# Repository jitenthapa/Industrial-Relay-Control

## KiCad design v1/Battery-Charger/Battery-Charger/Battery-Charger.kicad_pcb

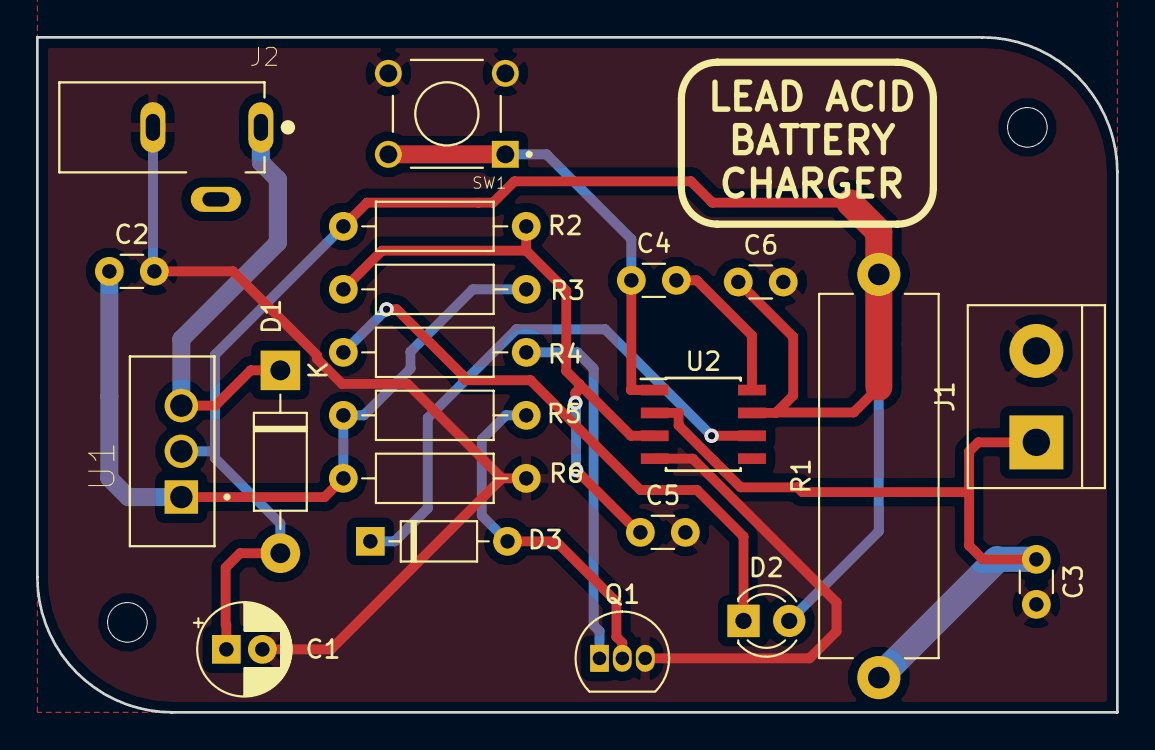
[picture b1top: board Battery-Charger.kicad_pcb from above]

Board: 2 copper layers, 60.0 x 37.5 mm, 23 parts (0 on the bottom side), 12 nets.

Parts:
C1: CP; CP_Radial_D5.0mm_P2.00mm
C2, C3, C4: C_Small; C_Disc_D3.0mm_W1.6mm_P2.50mm
C5: 10pf; C_Disc_D3.0mm_W1.6mm_P2.50mm
C6: 100nf; C_Disc_D3.0mm_W1.6mm_P2.50mm
D1: 1N4007; D_DO-41_SOD81_P10.16mm_Horizontal
D2: LED; LED_D3.0mm
D3: 1N4148; D_DO-35_SOD27_P7.62mm_Horizontal
J1: BATTERY; TerminalBlock_bornier-2_P5.08mm
J2: Jack-DC; DC-JACK
MOUNT1, MOUNT2: MountingHole_2.2mm_M2
Q1: 2N3906; TO-92_Inline
R1: R_Small; R_Axial_Power_L20.0mm_W6.4mm_P22.40mm
R2, R3: R_Small; R_Axial_DIN0207_L6.3mm_D2.5mm_P10.16mm_Horizontal
R4, R5, R6: R; R_Axial_DIN0207_L6.3mm_D2.5mm_P10.16mm_Horizontal
SW1: 1825910-2; TE_1825910-2
U1: LM338T; TO254P1054X470X1955-3
U2: LM301; SOIC-8_3.9x4.9mm_P1.27mm

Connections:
GND: C1.2, C2.2, C3.2, C5.2, C6.2, J1.2, J2.2, Q1.3, R6.2, SW1.3, SW1.4, U2.4
unnamed: C1.1, C6.1, D1.2, D2.2, R1.2, R2.1, U1.2, U2.7
unnamed: C2.1, R3.2, R5.1, R6.1, U1.1
unnamed: C3.1, J1.1, R1.1, U2.2
unnamed: C4.1, SW1.1, SW1.2, U2.1
unnamed: C4.2, U2.8
unnamed: C5.1, R2.2, R3.1, U2.3
unnamed: D1.1, J2.1, U1.3
unnamed: D2.1, R4.1
unnamed: D3.1, U2.6
unnamed: D3.2, Q1.2, R5.2
unnamed: Q1.1, R4.2

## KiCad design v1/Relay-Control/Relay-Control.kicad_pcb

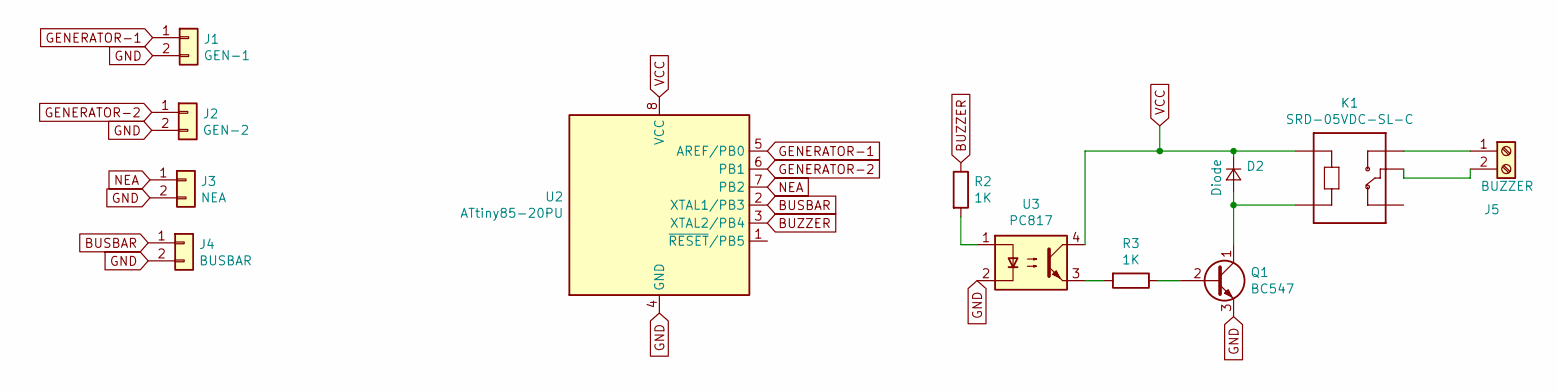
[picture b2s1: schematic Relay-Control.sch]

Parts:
D2: Diode; D_DO-27_P12.70mm_Horizontal
J1: GEN-1; Pin_Header_Straight_1x02_Pitch2.54mm
J2: GEN-2; Pin_Header_Straight_1x02_Pitch2.54mm
J3: NEA; Pin_Header_Straight_1x02_Pitch2.54mm
J4: BUSBAR; Pin_Header_Straight_1x02_Pitch2.54mm
J5: BUZZER; dual terminal-small-2
K1: SRD-05VDC-SL-C; RELAY_SRD-05VDC-SL-C
Q1: BC547; TO-92_Inline
R2, R3: 1K; R_0805_2012Metric
U2: ATtiny85-20PU; DIP-8_W7.62mm
U3: PC817; DIP-4_W7.62mm

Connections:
BUSBAR: J4.1, U2.2 (XTAL1/PB3)
BUZZER: R2.1, U2.3 (XTAL2/PB4)
GENERATOR-1: J1.1, U2.5 (AREF/PB0)
GENERATOR-2: J2.1, U2.6 (PB1)
GND: J1.2, J2.2, J3.2, J4.2, Q1.3 (E), U2.4 (GND), U3.2
NEA: J3.1, U2.7 (PB2)
unnamed: D2.2 (A), K1.A2, Q1.1 (C)
unnamed: J5.1, K1.NO
unnamed: J5.2, K1.COM
unnamed: Q1.2 (B), R3.1
unnamed: R2.2, U3.1
unnamed: R3.2, U3.3
VCC: D2.1 (K), K1.A1, U2.8 (VCC), U3.4

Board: 2 copper layers, 12 parts (0 on the bottom side), 13 nets, no tracks yet.

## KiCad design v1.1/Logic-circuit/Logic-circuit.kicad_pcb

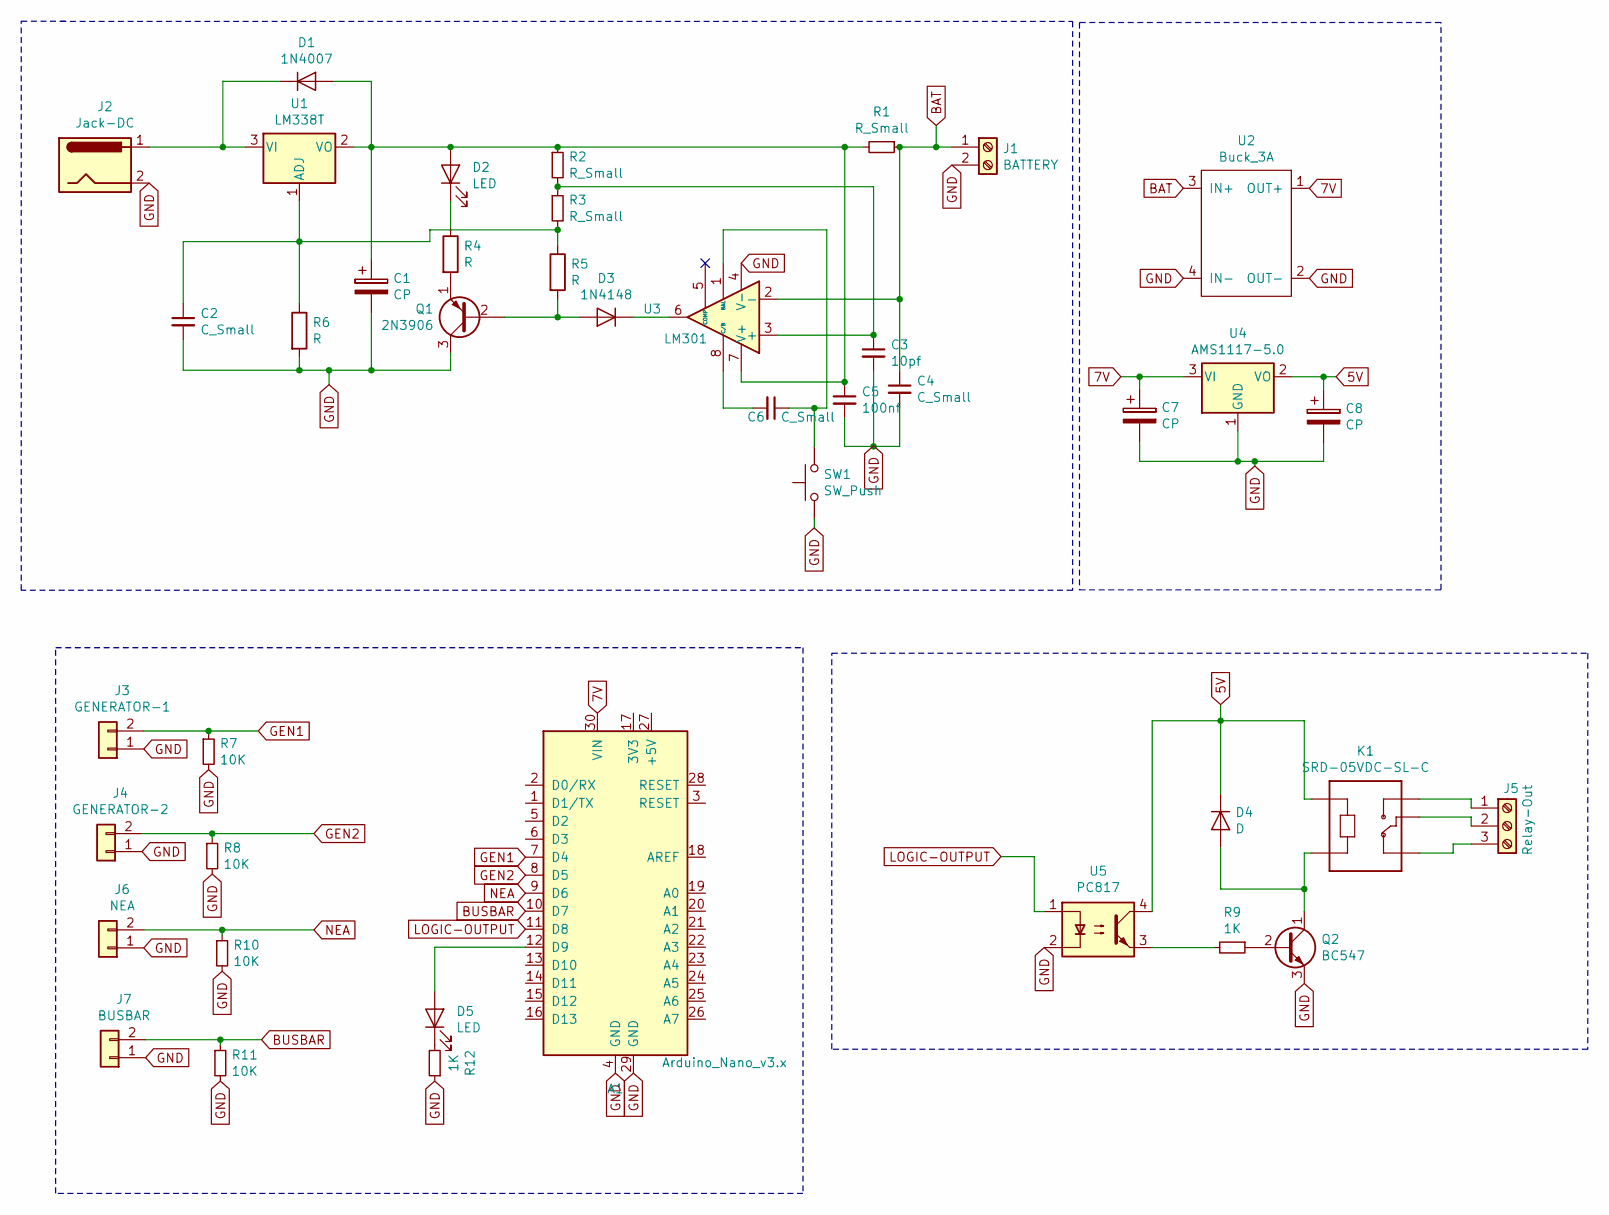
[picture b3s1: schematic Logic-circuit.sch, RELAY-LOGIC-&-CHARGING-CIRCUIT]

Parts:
A1: Arduino_Nano_v3.x; Arduino_Nano
C1, C7, C8: CP; CP_Radial_D5.0mm_P2.00mm
C2, C4, C6: C_Small; C_Disc_D3.0mm_W1.6mm_P2.50mm
C3: 10pf; C_Disc_D3.0mm_W1.6mm_P2.50mm
C5: 100nf; C_Disc_D3.0mm_W1.6mm_P2.50mm
D1: 1N4007; D_DO-41_SOD81_P10.16mm_Horizontal
D2, D5: LED; LED_D3.0mm
D3: 1N4148; D_DO-35_SOD27_P7.62mm_Horizontal
D4: D; D_SMA
J1: BATTERY; TerminalBlock_bornier-2_P5.08mm
J2: Jack-DC; DCJ200-10-A-XX-X_REVA
J3: GENERATOR-1; PinHeader_1x02_P2.54mm_Vertical
J4: GENERATOR-2; PinHeader_1x02_P2.54mm_Vertical
J5: Relay-Out; TerminalBlock_bornier-3_P5.08mm
J6: NEA; PinHeader_1x02_P2.54mm_Vertical
J7: BUSBAR; PinHeader_1x02_P2.54mm_Vertical
K1: SRD-05VDC-SL-C; RELAY_SRD-05VDC-SL-C-2
Q1: 2N3906; TO-92_Inline
Q2: BC547; TO-92_Inline
R1: R_Small; R_Axial_Power_L20.0mm_W6.4mm_P22.40mm
R2, R3: R_Small; R_Axial_DIN0207_L6.3mm_D2.5mm_P10.16mm_Horizontal
R4, R5, R6: R; R_Axial_DIN0207_L6.3mm_D2.5mm_P10.16mm_Horizontal
R7, R8, R10, R11: 10K; R_0805_2012Metric
R9, R12: 1K; R_0805_2012Metric
SW1: SW_Push; TE_1825910-2
U1: LM338T; TO-220-3_Vertical
U2: Buck_3A; Buck_3A-2
U3: LM301; SOIC-8_3.9x4.9mm_P1.27mm
U4: AMS1117-5.0; SOT-223-3_TabPin2
U5: PC817; DIP-4_W7.62mm

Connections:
5V: C8.1, D4.1 (K), K1.A1, U4.2 (VO), U5.4
7V: A1.30 (VIN), C7.1, U2.1 (OUT+), U4.3 (VI)
BAT: C4.1, J1.1, R1.1, U2.3 (IN+), U3.2 (-)
BUSBAR: A1.10 (D7), J7.2, R11.1
GEN1: A1.7 (D4), J3.2, R7.1
GEN2: A1.8 (D5), J4.2, R8.1
GND: A1.4 (GND), A1.29 (GND), C1.2, C2.2, C3.2, C4.2, C5.2, C7.2, C8.2, J1.2, J2.2, J3.1, J4.1, J6.1, J7.1, Q1.3 (C), Q2.3 (E), R6.2, R7.2, R8.2, R10.2, R11.2, R12.1, SW1.1, U2.2 (OUT-), U2.4 (IN-), U3.4 (V-), U4.1 (GND), U5.2
LOGIC-OUTPUT: A1.11 (D8), U5.1
NEA: A1.9 (D6), J6.2, R10.1
unnamed: A1.12 (D9), D5.2 (A)
unnamed: C1.1, C5.1, D1.2 (A), D2.2 (A), R1.2, R2.1, U1.2 (VO), U3.7 (V+)
unnamed: C2.1, R3.2, R5.1, R6.1, U1.1 (ADJ)
unnamed: C3.1, R2.2, R3.1, U3.3 (+)
unnamed: C6.1, SW1.2, U3.1 (BAL)
unnamed: C6.2, U3.8 (C/B)
unnamed: D1.1 (K), J2.1, U1.3 (VI)
unnamed: D2.1 (K), R4.1
unnamed: D3.1 (K), U3.6
unnamed: D3.2 (A), Q1.2 (B), R5.2
unnamed: D4.2 (A), K1.A2, Q2.1 (C)
unnamed: D5.1 (K), R12.2
unnamed: J5.1, K1.NO
unnamed: J5.2, K1.COM
unnamed: J5.3, K1.NC
unnamed: Q1.1 (E), R4.2
unnamed: Q2.2 (B), R9.1
unnamed: R9.2, U5.3

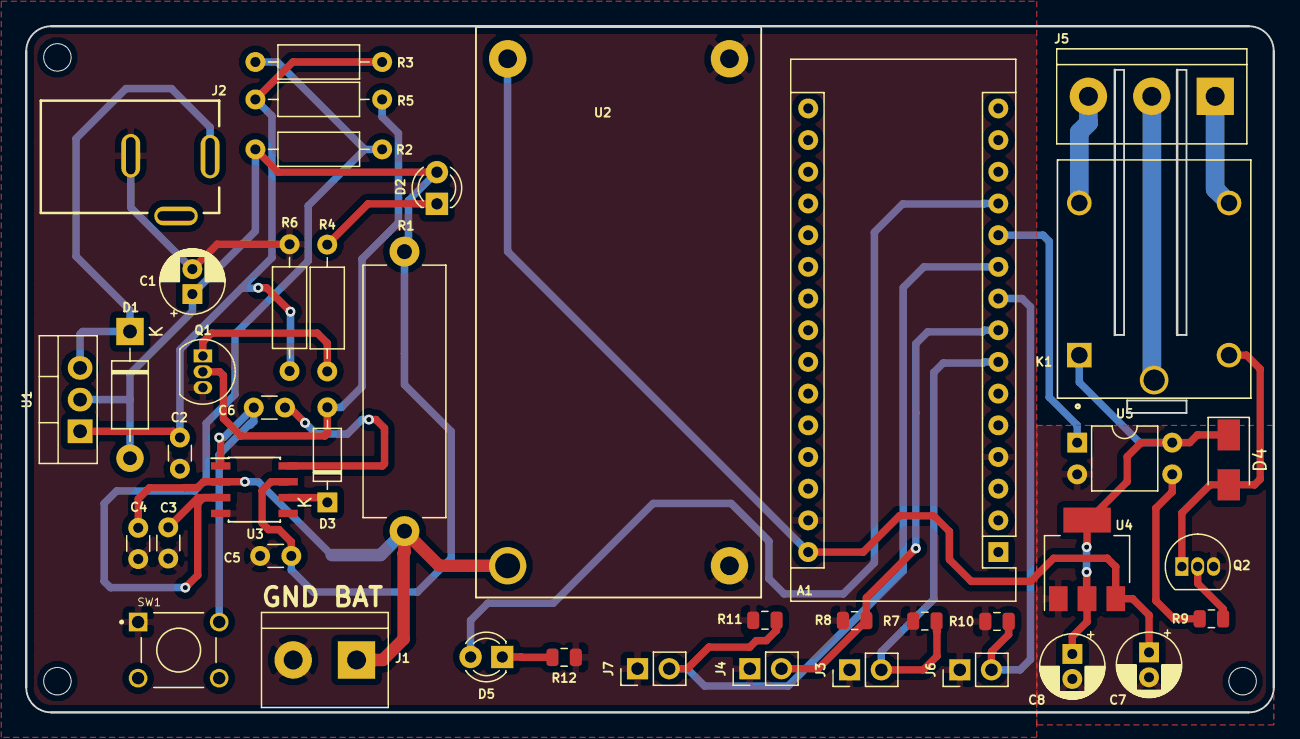
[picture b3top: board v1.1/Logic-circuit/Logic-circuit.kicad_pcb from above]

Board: 2 copper layers, 100.0 x 55.0 mm, 45 parts (0 on the bottom side), 27 nets.

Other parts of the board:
MH1, MH2, MH3: MountingHole_2.2mm_M2

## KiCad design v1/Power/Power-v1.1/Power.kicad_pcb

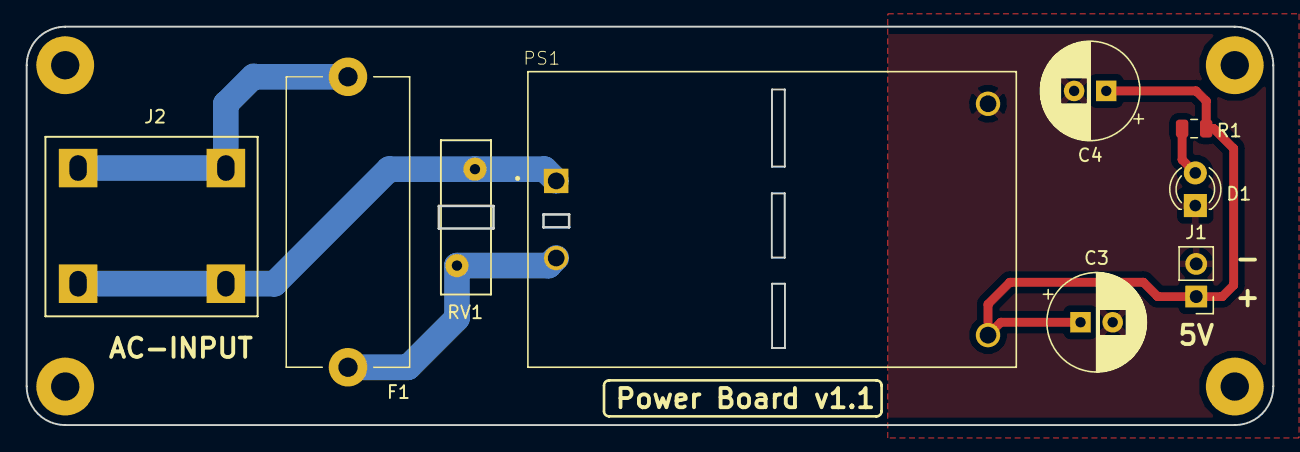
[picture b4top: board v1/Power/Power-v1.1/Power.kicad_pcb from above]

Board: 2 copper layers, 97.0 x 31.0 mm, 13 parts (0 on the bottom side), 6 nets.

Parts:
C3: 220uf; CP_Radial_D7.5mm_P2.50mm
C4: 1uf; CP_Radial_D7.5mm_P2.50mm
D1: LED; LED_D3.0mm
F1: Fuse; Fuseholder_Cylinder-5x20mm_Stelvio-Kontek_PTF78_Horizontal_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
J1: DC-POWER; Pin_Header_Straight_1x02_Pitch2.54mm
J2: AC; dual terminal-large
MH1, MH2, MH2#2, MH2#3: MountingHole_2.2mm_M2
PS1: POWER SUPPLY; CONV_HLK-5M05-Large-holes
R1: 220; R_0805_2012Metric
RV1: Varistor; RV_Disc_D12mm_W3.9mm_P7.5mm

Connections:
5V: C3.1, C4.1, J1.1, PS1.4, R1.2
GND: C3.2, C4.2, D1.1, J1.2, PS1.3
unnamed: D1.2, R1.1
unnamed: F1.1, PS1.2, RV1.1
unnamed: F1.2, J2.2
unnamed: J2.1, PS1.1, RV1.2

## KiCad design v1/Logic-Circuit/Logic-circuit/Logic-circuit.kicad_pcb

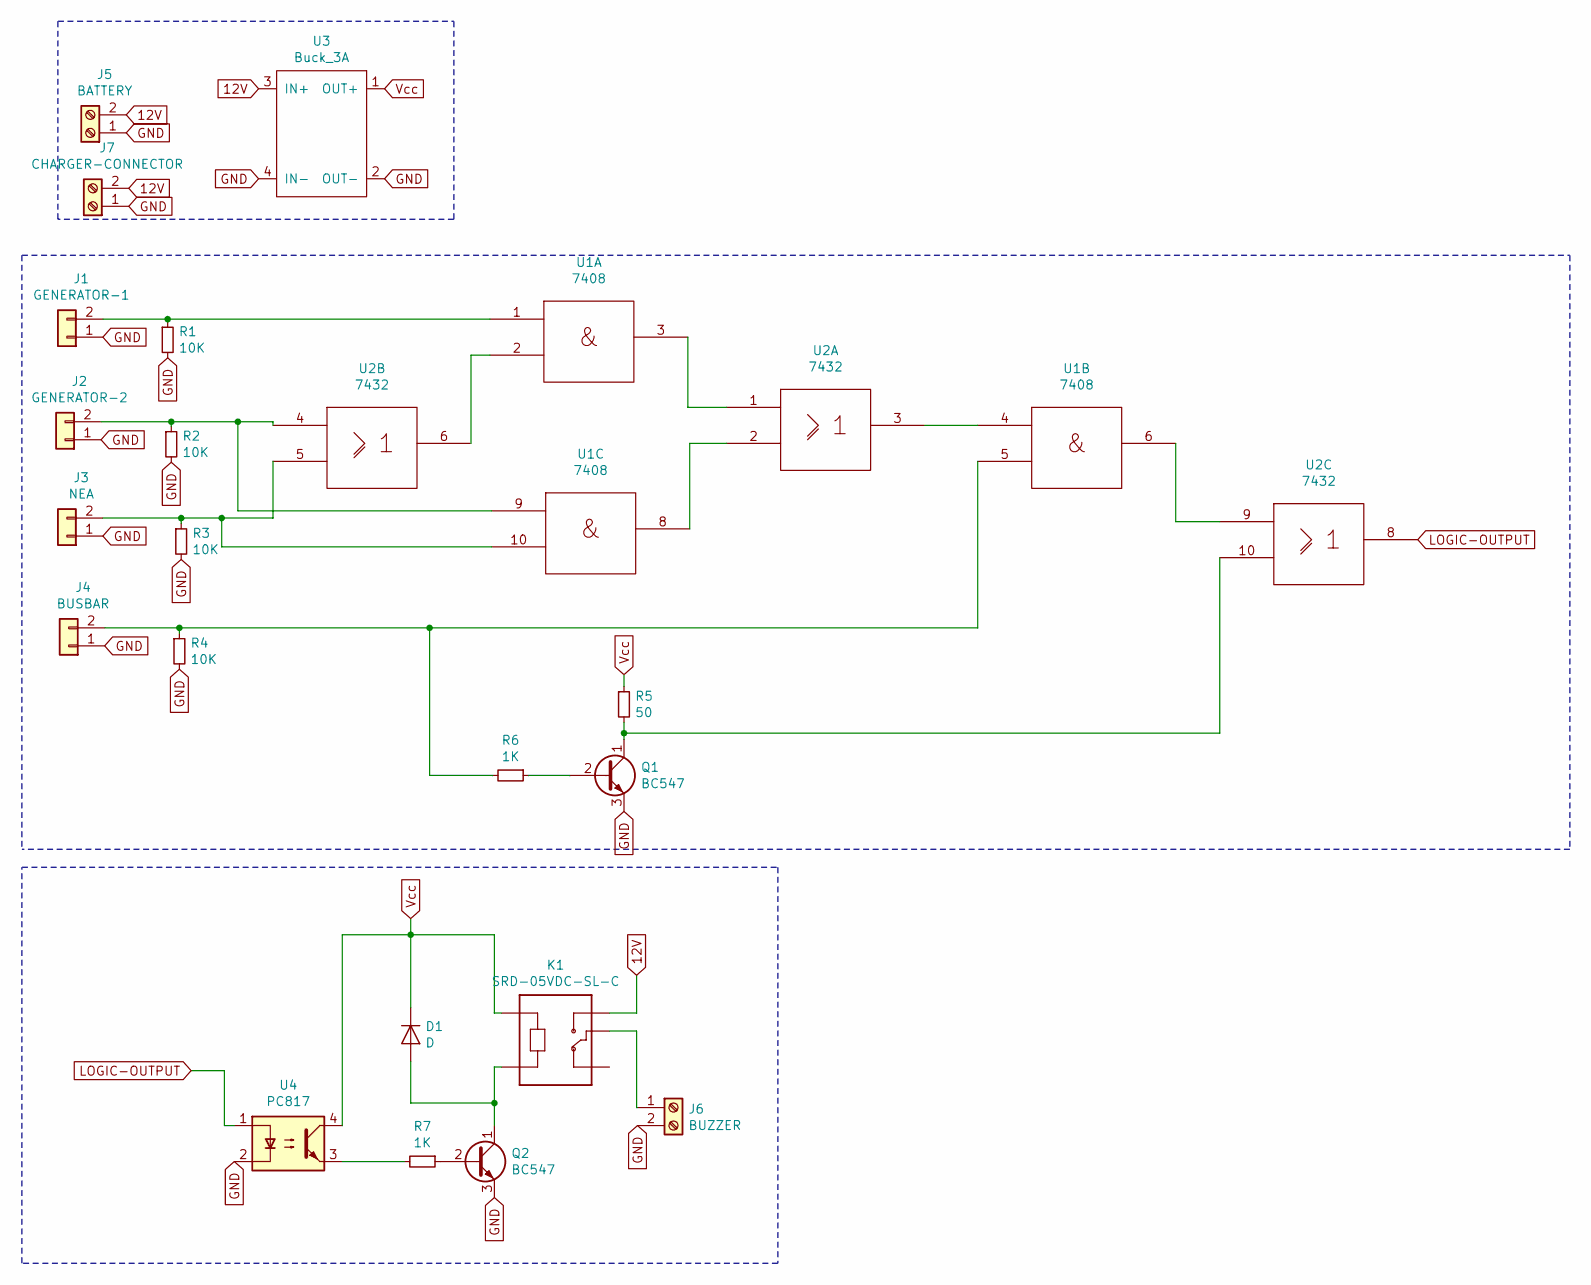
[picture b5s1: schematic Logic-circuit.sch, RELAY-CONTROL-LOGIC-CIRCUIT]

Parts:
D1: D; D_SOD-123
J1: GENERATOR-1; PinHeader_1x02_P2.54mm_Vertical
J2: GENERATOR-2; PinHeader_1x02_P2.54mm_Vertical
J3: NEA; PinHeader_1x02_P2.54mm_Vertical
J4: BUSBAR; PinHeader_1x02_P2.54mm_Vertical
J5: BATTERY; TerminalBlock_bornier-2_P5.08mm
J6: BUZZER; TerminalBlock_bornier-2_P5.08mm
J7: CHARGER-CONNECTOR; TerminalBlock_bornier-2_P5.08mm
K1: SRD-05VDC-SL-C; RELAY_SRD-05VDC-SL-C-2
Q1, Q2: BC547; TO-92_Inline
R1, R2, R3, R4: 10K; R_0805_2012Metric
R5: 50; R_0805_2012Metric
R6, R7: 1K; R_0805_2012Metric
U1: 7408; DIP-14_W7.62mm
U2: 7432; DIP-14_W7.62mm
U3: Buck_3A; Buck_3A-2
U4: PC817; DIP-4_W7.62mm

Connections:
12V: J5.2, J7.2, K1.NO, U3.3 (IN+)
GND: J1.1, J2.1, J3.1, J4.1, J5.1, J6.2, J7.1, Q1.3 (E), Q2.3 (E), R1.2, R2.2, R3.2, R4.2, U3.2 (OUT-), U3.4 (IN-), U4.2
Gnd: U1.7 (Gnd), U2.7 (Gnd)
LOGIC-OUTPUT: U2.8, U4.1
unnamed: D1.2 (A), K1.A2, Q2.1 (C)
unnamed: J1.2, R1.1, U1.1
unnamed: J2.2, R2.1, U1.9, U2.4
unnamed: J3.2, R3.1, U1.10, U2.5
unnamed: J4.2, R4.1, R6.2, U1.5
unnamed: J6.1, K1.COM
unnamed: Q1.1 (C), R5.2, U2.10
unnamed: Q1.2 (B), R6.1
unnamed: Q2.2 (B), R7.1
unnamed: R7.2, U4.3
unnamed: U1.2, U2.6
unnamed: U1.3, U2.1
unnamed: U1.4, U2.3
unnamed: U1.6, U2.9
unnamed: U1.8, U2.2
Vcc: D1.1 (K), K1.A1, R5.1, U1.14 (Vcc), U2.14 (Vcc), U3.1 (OUT+), U4.4

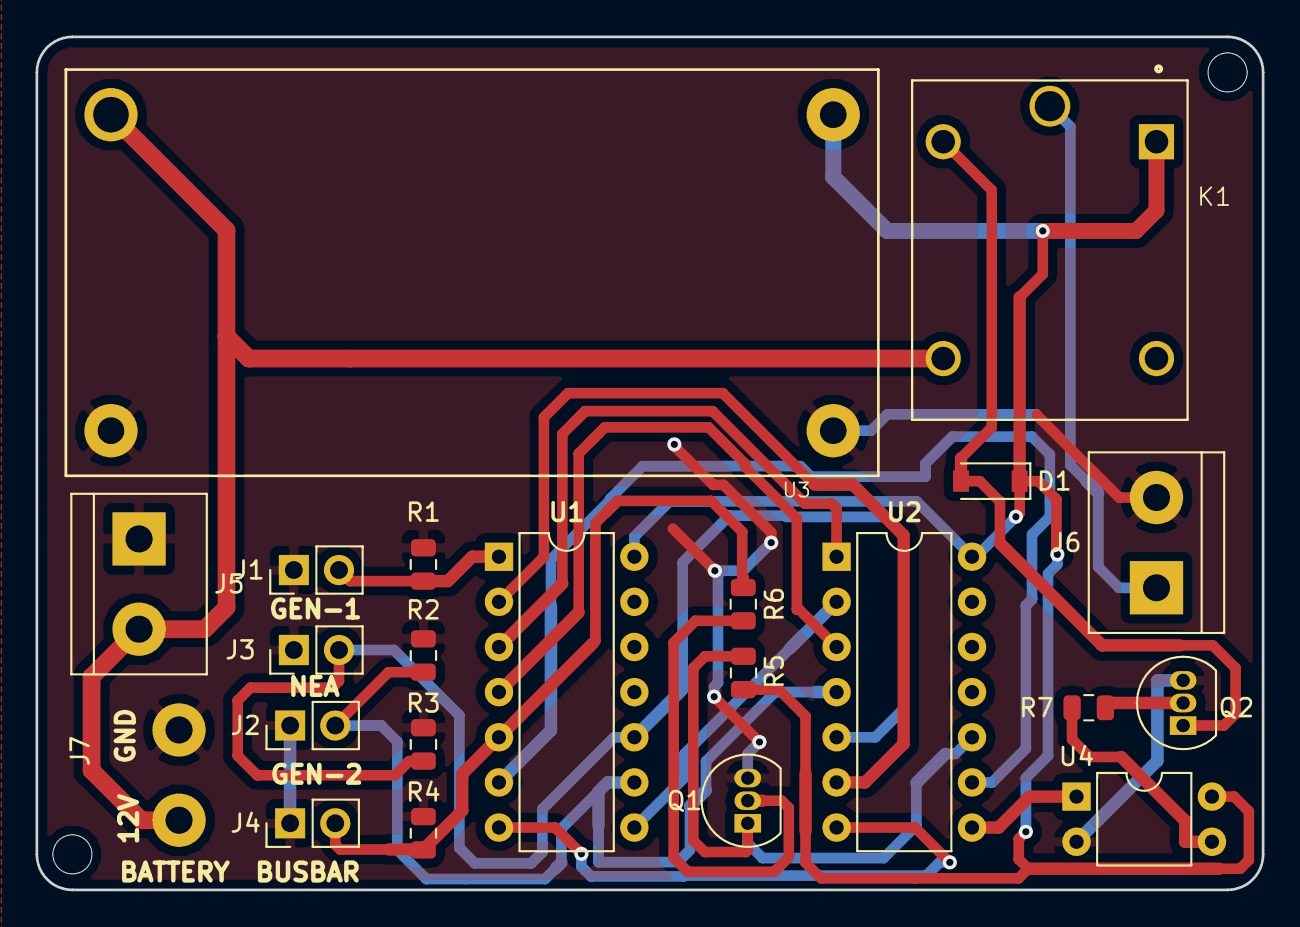
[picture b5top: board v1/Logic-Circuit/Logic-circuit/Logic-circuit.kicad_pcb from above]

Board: 2 copper layers, 69.0 x 48.0 mm, 24 parts (0 on the bottom side), 20 nets.

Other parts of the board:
MH1, MH2: MountingHole_2.2mm_M2

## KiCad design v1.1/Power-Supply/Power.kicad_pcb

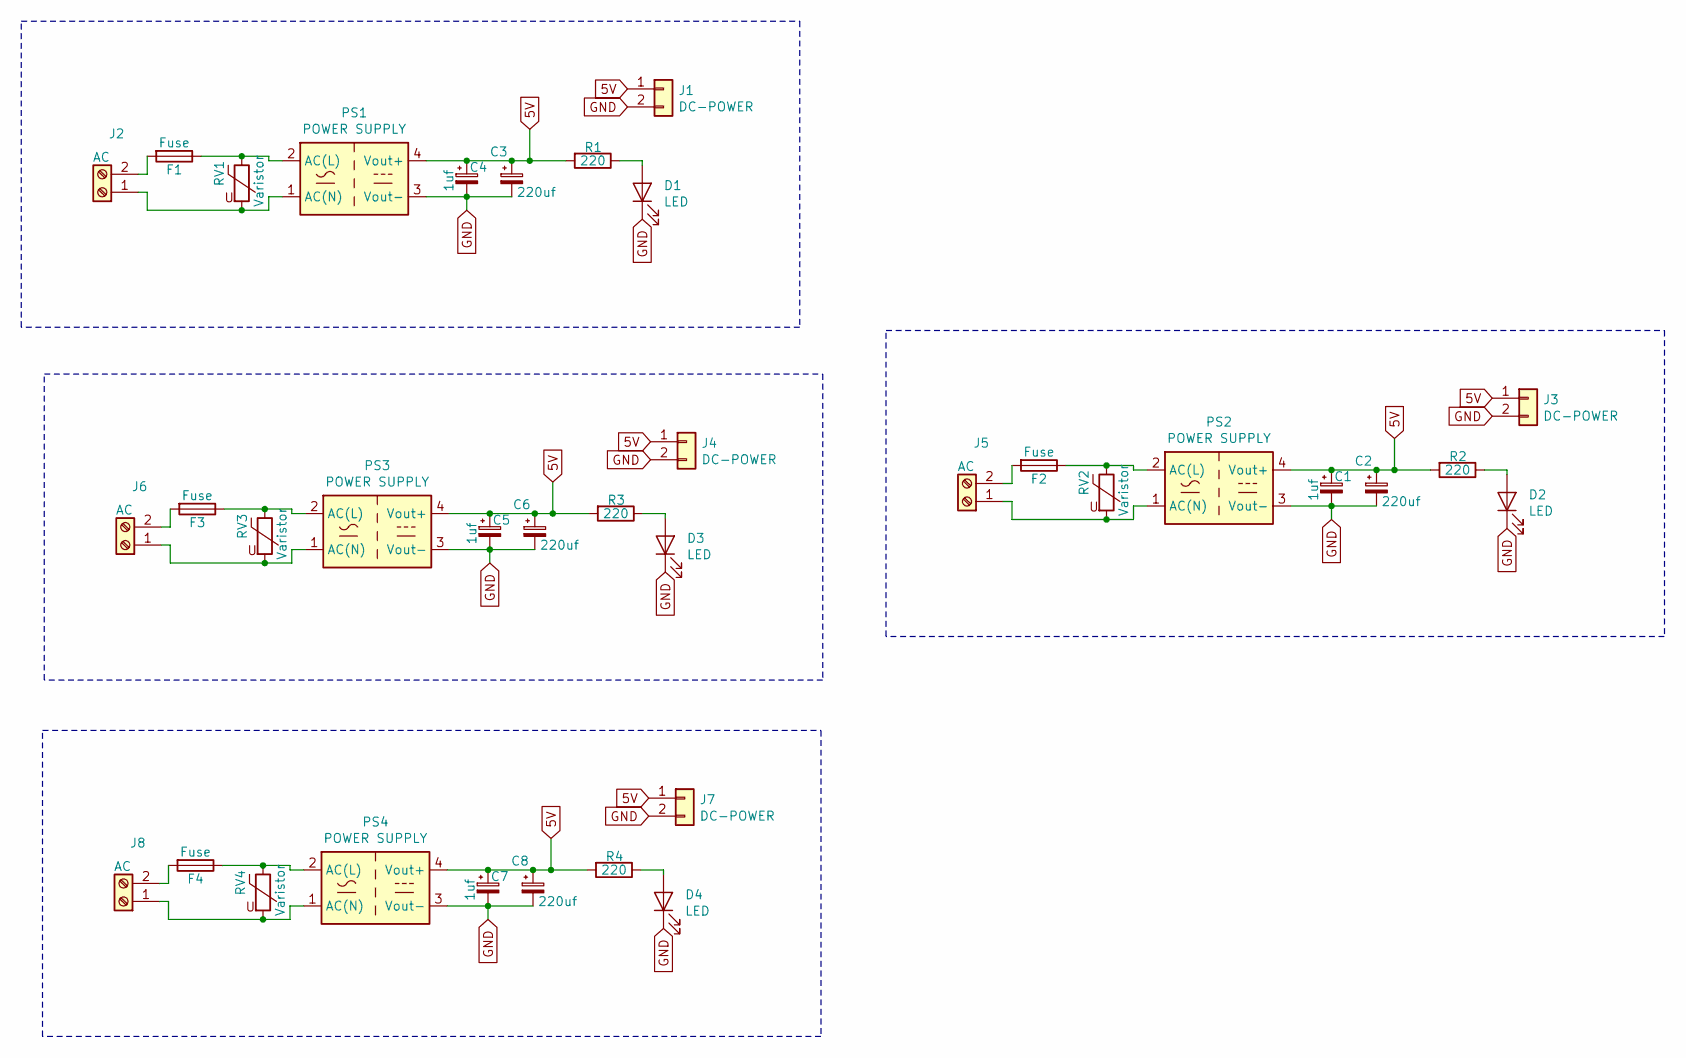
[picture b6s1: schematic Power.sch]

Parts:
C1, C4, C5, C7: 1uf; CP_Radial_D7.5mm_P2.50mm
C2, C3, C6, C8: 220uf; CP_Radial_D7.5mm_P2.50mm
D1, D2, D3, D4: LED; LED_D3.0mm
F1, F2, F3, F4: Fuse; Fuseholder_Cylinder-5x20mm_Stelvio-Kontek_PTF78_Horizontal_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
J1, J3, J4, J7: DC-POWER; Pin_Header_Straight_1x02_Pitch2.54mm
J2, J5, J6, J8: AC; dual terminal-large
PS1, PS2, PS3, PS4: POWER SUPPLY; CONV_HLK-5M05-Large-holes
R1, R2, R3, R4: 220; R_0805_2012Metric
RV1, RV2, RV3, RV4: Varistor; RV_Disc_D12mm_W3.9mm_P7.5mm

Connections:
5V: C1.1, C2.1, C3.1, C4.1, C5.1, C6.1, C7.1, C8.1, J1.1, J3.1, J4.1, J7.1, PS1.4 (Vout+), PS2.4 (Vout+), PS3.4 (Vout+), PS4.4 (Vout+), R1.2, R2.2, R3.2, R4.2
GND: C1.2, C2.2, C3.2, C4.2, C5.2, C6.2, C7.2, C8.2, D1.1 (K), D2.1 (K), D3.1 (K), D4.1 (K), J1.2, J3.2, J4.2, J7.2, PS1.3 (Vout-), PS2.3 (Vout-), PS3.3 (Vout-), PS4.3 (Vout-)
unnamed: D1.2 (A), R1.1
unnamed: D2.2 (A), R2.1
unnamed: D3.2 (A), R3.1
unnamed: D4.2 (A), R4.1
unnamed: F1.1, PS1.2 (AC(L)), RV1.1
unnamed: F1.2, J2.2
unnamed: F2.1, PS2.2 (AC(L)), RV2.1
unnamed: F2.2, J5.2
unnamed: F3.1, PS3.2 (AC(L)), RV3.1
unnamed: F3.2, J6.2
unnamed: F4.1, PS4.2 (AC(L)), RV4.1
unnamed: F4.2, J8.2
unnamed: J2.1, PS1.1 (AC(N)), RV1.2
unnamed: J5.1, PS2.1 (AC(N)), RV2.2
unnamed: J6.1, PS3.1 (AC(N)), RV3.2
unnamed: J8.1, PS4.1 (AC(N)), RV4.2

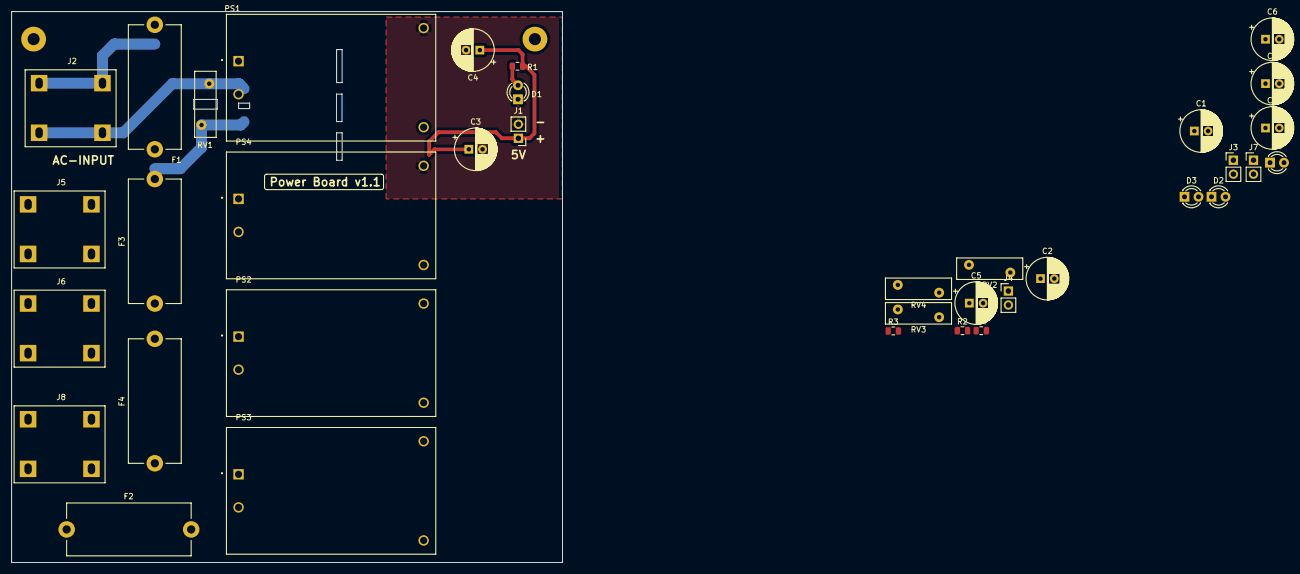
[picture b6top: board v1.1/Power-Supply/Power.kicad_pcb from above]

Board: 2 copper layers, 100.0 x 100.0 mm, 38 parts (0 on the bottom side), 18 nets.

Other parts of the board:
MH1, MH2: MountingHole_2.2mm_M2

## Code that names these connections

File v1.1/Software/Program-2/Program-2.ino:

//This is the program that worked in the previous system
// Finalized on 7/10/2022
#define gen1 7
#define gen2 5
#define nea 4
#define busbar 6
#define outputpin 8
#define outputled 9

void setup() {
  // initialize digital pin LED_BUILTIN as an output.
  pinMode(gen1, INPUT);
  pinMode(gen2, INPUT);
  pinMode(nea, INPUT);
  pinMode(busbar, INPUT);
  pinMode(outputpin, OUTPUT);
  pinMode(outputled, OUTPUT);
}

void loop() {

  while (((digitalRead(busbar) == 0)) || (((digitalRead(nea) == 1) && (digitalRead(busbar) == 1)) && ((digitalRead(gen1) == 1) || (digitalRead(gen2))))) {
    digitalWrite(outputpin, HIGH);
    digitalWrite(outputled, HIGH);
  }
  digitalWrite(outputpin, LOW);
  digitalWrite(outputled, LOW);
}

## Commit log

2022-07-10 relay control
